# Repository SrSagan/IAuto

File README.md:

# IAuto

IAuto is a little car that's controlled by an artificial intelligence, the brain of the operations is a Raspberry pi 3 that's controlling 2 DC motors and has a camera connected to it.

# Objectives

This project is merely for education, not only learn how to code advanced algorithms but also to use as an example for other poeple who might be trying to learn something similar.

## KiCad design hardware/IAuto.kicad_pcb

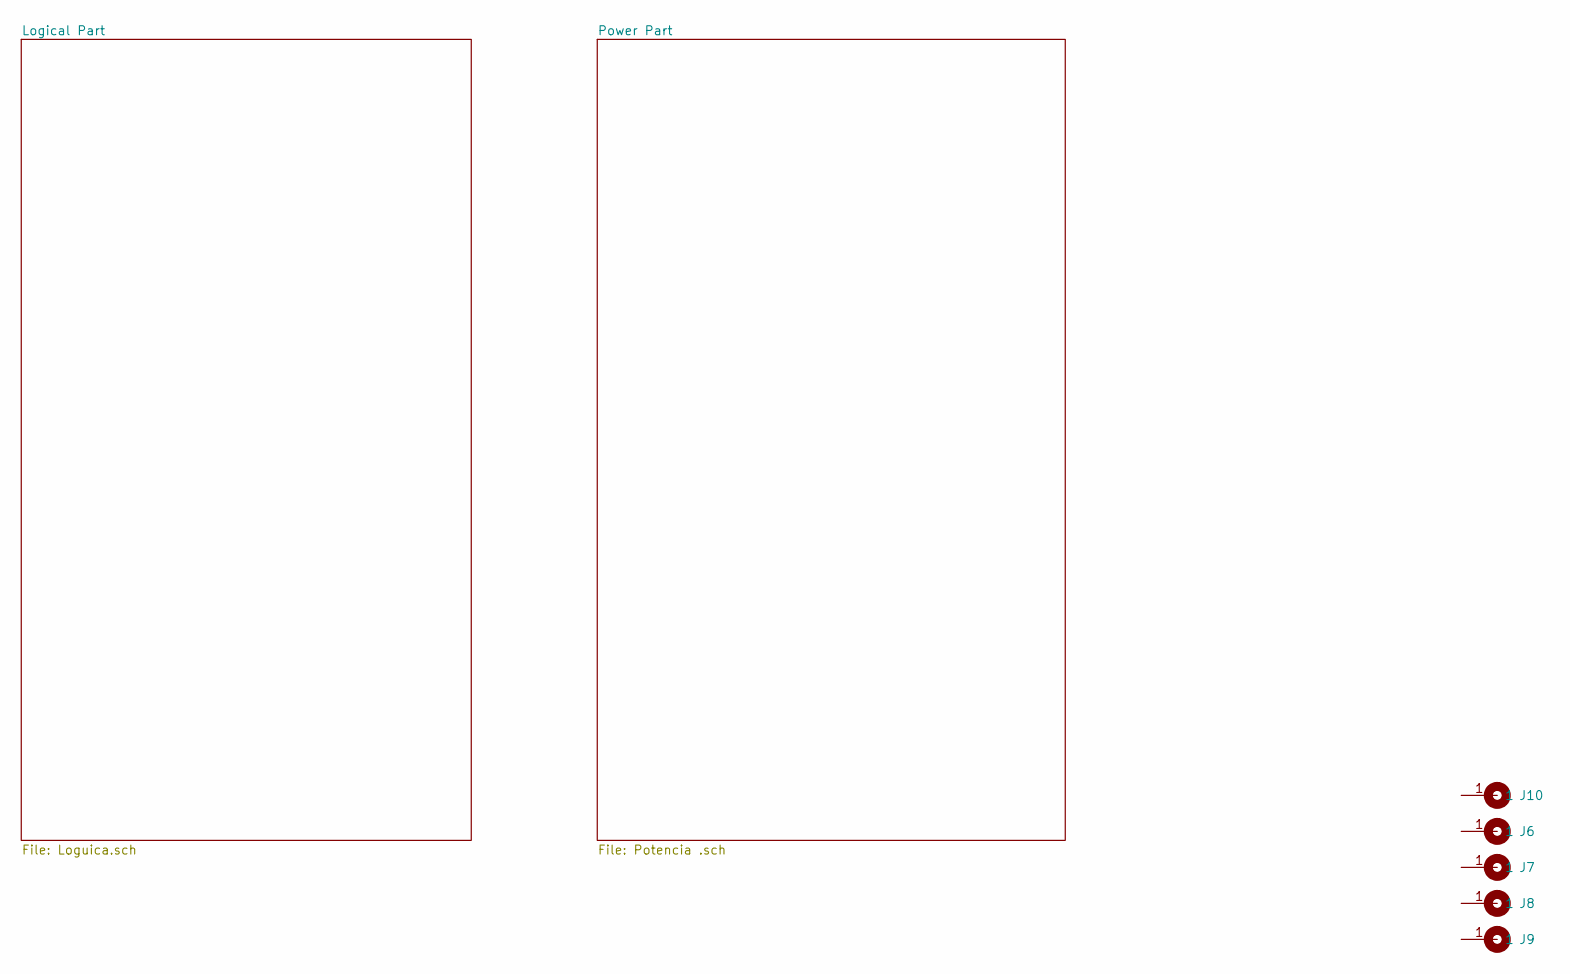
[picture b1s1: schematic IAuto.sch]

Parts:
J6, J7, J8, J9: Cable_PAD; Separador_M3_10mm
J10: Cable_PAD; LOGO_EESTN5

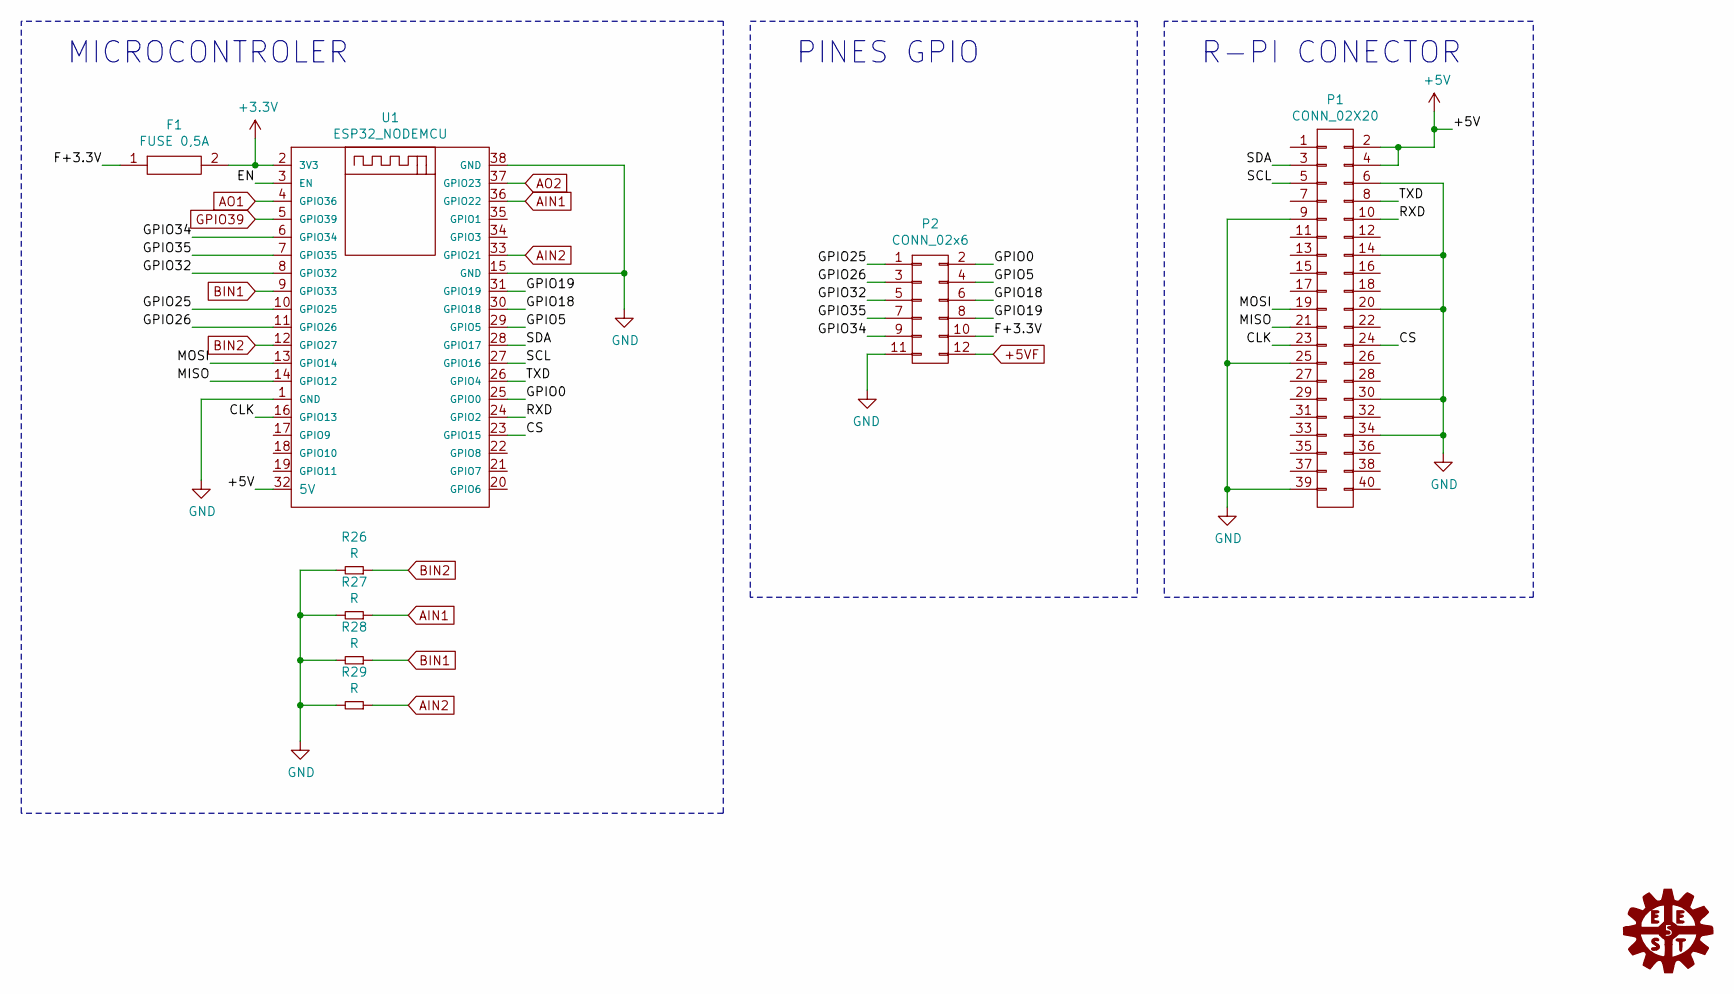
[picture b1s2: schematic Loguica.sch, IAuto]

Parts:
F1: FUSE 0,5A; R_1206
P1: CONN_02X20; Pin_Header_Straight_2x20
P2: CONN_02x6; Pin_strip_2x6
R26, R27, R28, R29: R; R_0805
U1: ESP32_NODEMCU; NodeMCU-ESP32

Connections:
+3V3: F1.2, U1.2 (3V3); also elsewhere on the board
+5V: P1.2, P1.4, U1.32 (5V); also elsewhere on the board
+5VF: P2.12; also elsewhere on the board
/Logical Part/CLK: P1.23, U1.16 (GPIO13)
/Logical Part/CS: P1.24, U1.23 (GPIO15)
/Logical Part/F+3.3V: F1.1, P2.10
/Logical Part/GPIO0: P2.2, U1.25 (GPIO0)
/Logical Part/GPIO5: P2.4, U1.29 (GPIO5)
/Logical Part/GPIO18: P2.6, U1.30 (GPIO18)
/Logical Part/GPIO19: P2.8, U1.31 (GPIO19)
/Logical Part/GPIO25: P2.1, U1.10 (GPIO25)
/Logical Part/GPIO26: P2.3, U1.11 (GPIO26)
/Logical Part/GPIO32: P2.5, U1.8 (GPIO32)
/Logical Part/GPIO34: P2.9, U1.6 (GPIO34)
/Logical Part/GPIO35: P2.7, U1.7 (GPIO35)
/Logical Part/MISO: P1.21, U1.14 (GPIO12)
/Logical Part/MOSI: P1.19, U1.13 (GPIO14)
/Logical Part/RXD: P1.10, U1.24 (GPIO2)
/Logical Part/SCL: P1.5, U1.27 (GPIO16)
/Logical Part/SDA: P1.3, U1.28 (GPIO17)
/Logical Part/TXD: P1.8, U1.26 (GPIO4)
AIN1: R27.1, U1.36 (GPIO22); also elsewhere on the board
AIN2: R29.1, U1.33 (GPIO21); also elsewhere on the board
AO1: U1.4 (GPIO36); also elsewhere on the board
AO2: U1.37 (GPIO23); also elsewhere on the board
BIN1: R28.1, U1.9 (GPIO33); also elsewhere on the board
BIN2: R26.1, U1.12 (GPIO27); also elsewhere on the board
GND: P1.6, P1.9, P1.14, P1.20, P1.25, P1.30, P1.34, P1.39, P2.11, R26.2, R27.2, R28.2, R29.2, U1.1 (GND), U1.15 (GND), U1.38 (GND); also elsewhere on the board
GPIO39: U1.5 (GPIO39); also elsewhere on the board

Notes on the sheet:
MICROCONTROLER
R-PI CONECTOR
PINES GPIO

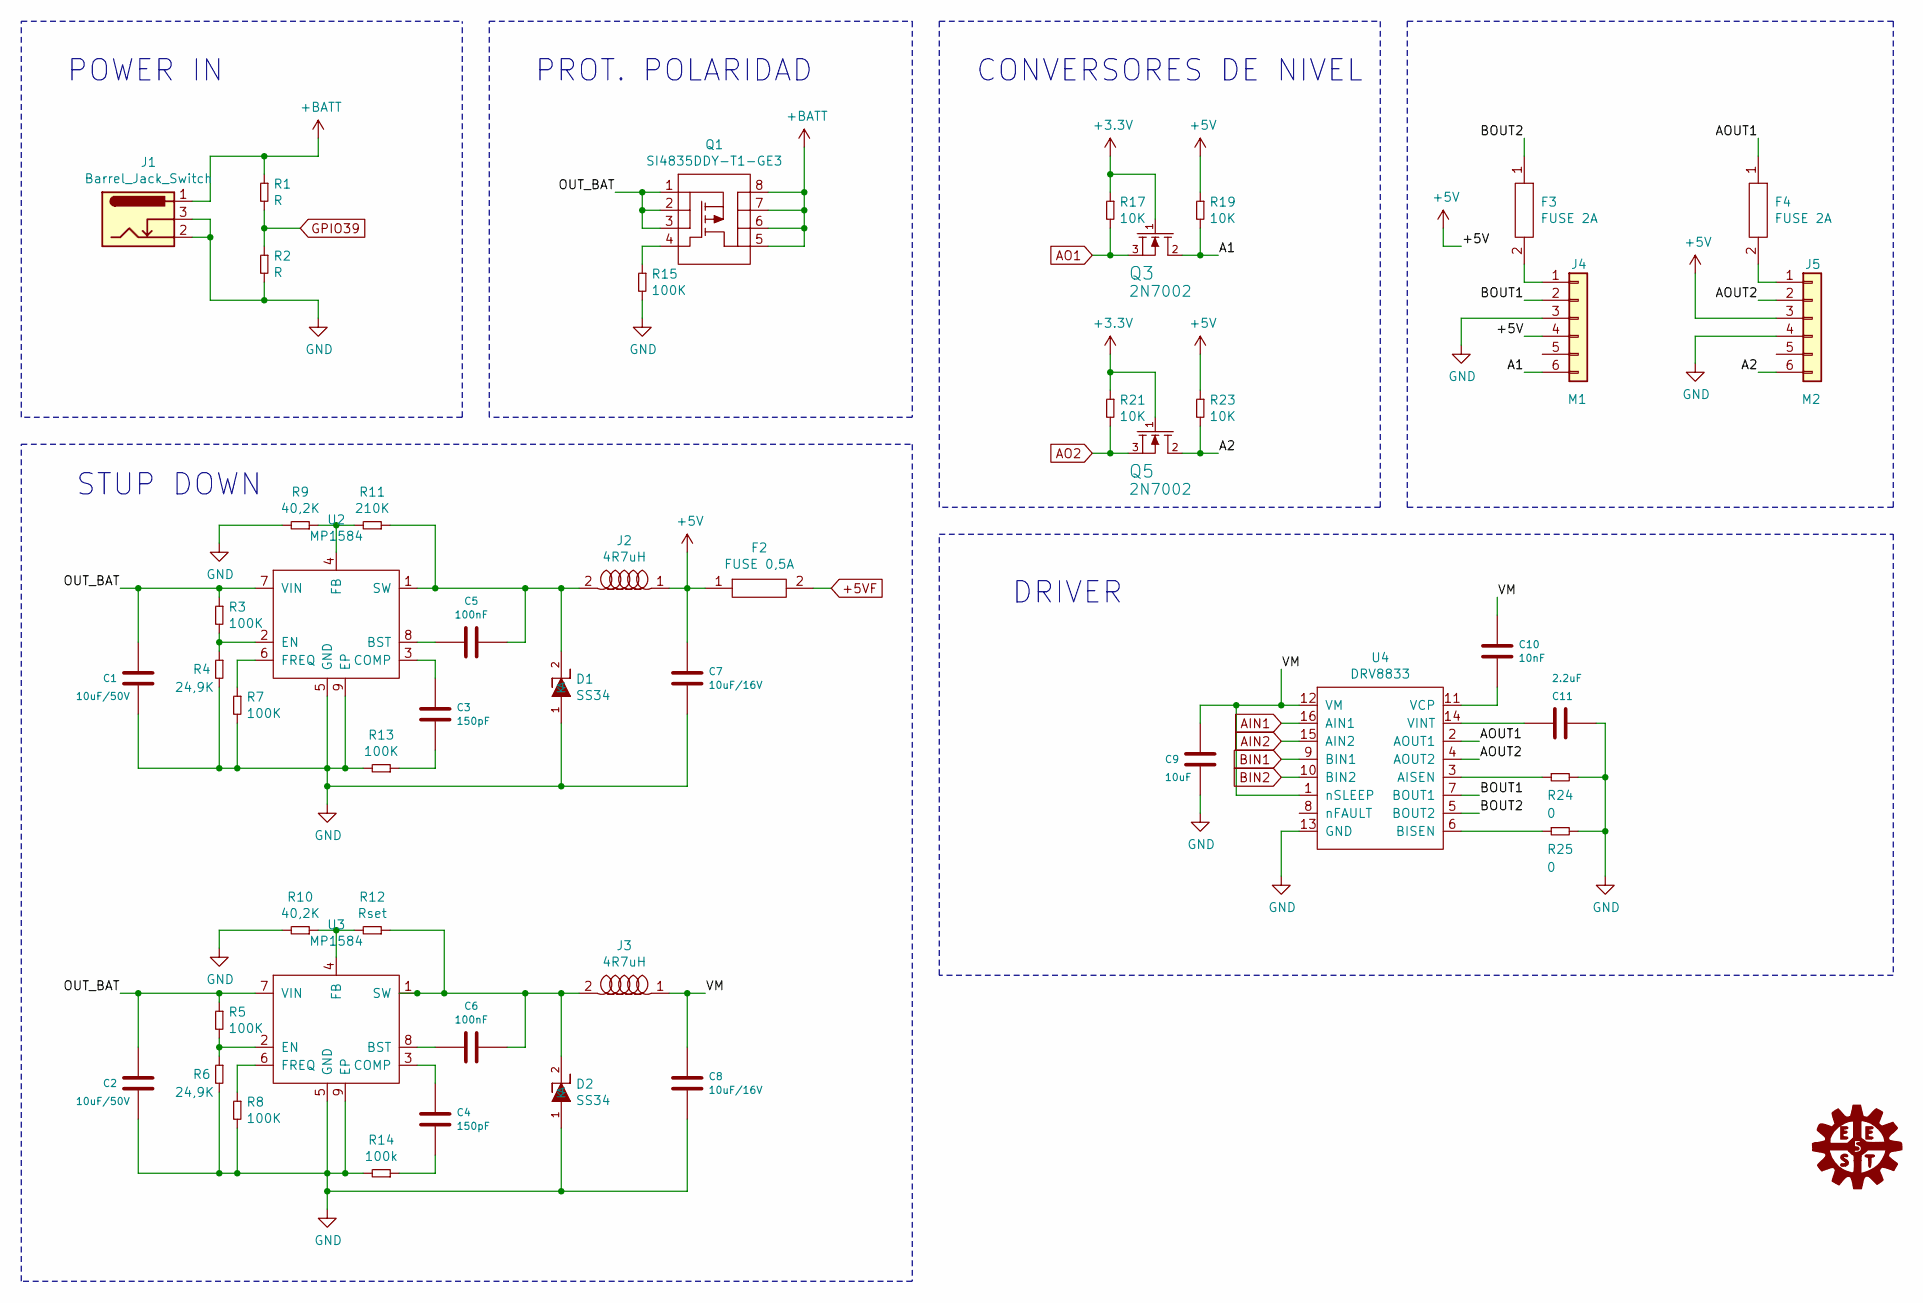
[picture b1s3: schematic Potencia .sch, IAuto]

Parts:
C1, C2: 10uF/50V; C_1206
C3, C4: 150pF; C_0805
C5, C6: 100nF; C_0805
C7, C8: 10uF/16V; C_1206
C9: 10uF; C_1206
C10: 10nF; C_0805
C11: 2.2uF; C_0805
D1, D2: SS34; DO-214AB
F2: FUSE 0,5A; R_1206
F3, F4: FUSE 2A; FUSC5141X200N
J1: Barrel_Jack_Switch; Jack_hembra_DC_barrel
J2, J3: 4R7uH; SRP65404R7M
J4: M1; Conector_jst_6_pins_2mm
J5: M2; Conector_jst_6_pins_2mm
Q1: SI4835DDY-T1-GE3; SSOP-8
Q3, Q5: 2N7002; SOT23
R1, R2: R; R_0805
R3, R5, R7, R8, R13, R15: 100K; R_0805
R4, R6: 24,9K; R_0805
R9, R10: 40,2K; R_0805
R11: 210K; R_0805
R12: Rset; R_0805
R14: 100k; R_0805
R17, R19, R21, R23: 10K; R_0805
R24, R25: 0; R_0805
U2, U3: MP1584; SOIC8E
U4: DRV8833; HTSSOP

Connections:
+3V3: Q3.1 (G), Q5.1 (G), R17.1, R21.1; also elsewhere on the board
+5V: C7.2, F2.1, J2.1, J4.4, J5.3, R19.1, R23.1; also elsewhere on the board
+5VF: F2.2; also elsewhere on the board
+BATT: J1.1, Q1.5, Q1.6, Q1.7, Q1.8, R1.1
/Power Part/A1: J4.6, Q3.2 (D), R19.2
/Power Part/A2: J5.6, Q5.2 (D), R23.2
/Power Part/AOUT1: F4.1, U4.2 (AOUT1)
/Power Part/AOUT2: J5.2, U4.4 (AOUT2)
/Power Part/BOUT1: J4.2, U4.7 (BOUT1)
/Power Part/BOUT2: F3.1, U4.5 (BOUT2)
/Power Part/OUT_BAT: C1.2, C2.2, Q1.1, Q1.2, Q1.3, R3.1, R5.1, U2.7 (VIN), U3.7 (VIN)
AIN1: U4.16 (AIN1); also elsewhere on the board
AIN2: U4.15 (AIN2); also elsewhere on the board
AO1: Q3.3 (S), R17.2; also elsewhere on the board
AO2: Q5.3 (S), R21.2; also elsewhere on the board
BIN1: U4.9 (BIN1); also elsewhere on the board
BIN2: U4.10 (BIN2); also elsewhere on the board
GND: C1.1, C2.1, C7.1, C8.1, C9.2, C11.1, D1.1 (A), D2.1 (A), J1.2, J1.3, J4.3, J5.4, R2.2, R4.2, R6.2, R7.2, R8.2, R9.2, R10.2, R13.2, R14.2, R15.2, R24.2, R25.2, U2.5 (GND), U2.9 (EP), U3.5 (GND), U3.9 (EP), U4.13 (GND), U4.17; also elsewhere on the board
GPIO39: R1.2, R2.1; also elsewhere on the board
unnamed: C3.1, R13.1
unnamed: C3.2, U2.3 (COMP)
unnamed: C4.1, R14.1
unnamed: C4.2, U3.3 (COMP)
unnamed: C5.1, U2.8 (BST)
unnamed: C5.2, D1.2 (K), J2.2, R11.1, U2.1 (SW)
unnamed: C6.1, U3.8 (BST)
unnamed: C6.2, D2.2 (K), J3.2, R12.1, U3.1 (SW)
unnamed: C10.2, U4.11 (VCP)
unnamed: C11.2, U4.14 (VINT)
unnamed: F3.2, J4.1
unnamed: F4.2, J5.1
unnamed: Q1.4, R15.1
unnamed: R3.2, R4.1, U2.2 (EN)
unnamed: R5.2, R6.1, U3.2 (EN)
unnamed: R7.1, U2.6 (FREQ)
unnamed: R8.1, U3.6 (FREQ)
unnamed: R10.1, R12.2, U3.4 (FB)
unnamed: R9.1, R11.2, U2.4 (FB)
unnamed: R24.1, U4.3 (AISEN)
unnamed: R25.1, U4.6 (BISEN)

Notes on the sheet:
POWER IN
CONVERSORES DE NIVEL
PROT. POLARIDAD
STUP DOWN
DRIVER

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
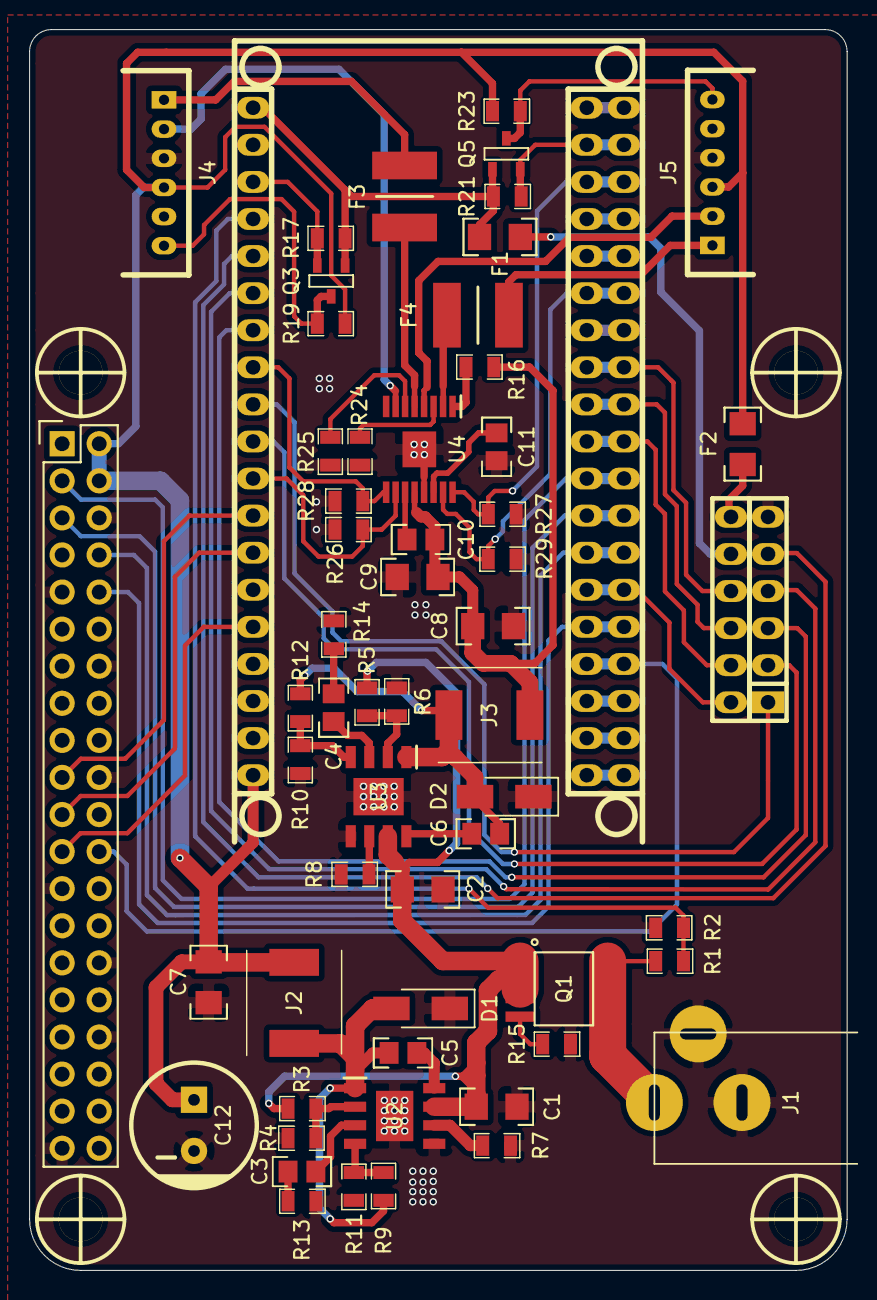
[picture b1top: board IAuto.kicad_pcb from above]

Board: 2 copper layers, 56.0 x 85.0 mm, 62 parts (0 on the bottom side), 60 nets.

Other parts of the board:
C12: 1000uF/16V; CAP_ELEC_8x11.5mm
R16: 47k; R_0805

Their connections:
+5V: C12.1; also elsewhere on the board
GND: C12.2; also elsewhere on the board

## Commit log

2021-06-22 readme
2021-07-15 docker
2021-07-29 santi simp
2021-08-05 Code
2021-08-05 control
2021-08-12 suciaCarpeta
2021-08-12 espBluetooth
2021-08-12 Arreglos
2021-08-12 library
2021-08-12 main
2021-08-26 hardware
2021-08-26 libreria
2021-08-26 camera
2021-08-31 haedware
2021-09-09 anteultimos_cambios
2021-09-15 ultimos cambios
2021-09-17 Final
2021-09-22 image recognition
2021-09-23 add dockerfile
2021-10-06 minor fixes
2021-10-07 Minor fixes and exposicion mode
2021-10-20 somestuff
2021-10-22 hardware_v20
2021-11-25 cosas
2021-11-29 lauty
